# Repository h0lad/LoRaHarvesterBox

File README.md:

## What is this thing?

This generic LoRa base board is built around the ST STM32WLE5CC (RAK3172) and the TI BQ25570 energy harvester.

It is suitable for a wide range of applications, including:

- Meshtastic (router, sensor) or Meshcore
- LoRaWAN sensors
- Generic raw LoRa devices
- Or virtually any other custom project (ham balloon? Transmitter for tracking penguins?) that utilizes the modulation schemes (FSK, GFSK, MSK, GMSK) of the SX1262

For persistent data storage, an optional FRAM IC (Infineon FM24V10) can be added using I²C. A variety of sensors can additonaly integrated through I²C, SPI (on the back), or USART interfaces.

The power supply design is highly flexible: alongside standard JST-PH connectors, the board also supports very small LiPo batteries (commonly used in in-ear headphones or Bluetooth headsets), which can be soldered directly. Such batteries are readily available on AliExpress (e.g. 501010). The TI BQ25570 also supports exotic storages like Supercaps, LTO, etc.

## Features

### Energy

- Capable of handling a huge variety of energy storages: LiPo, LiFePo4, LTO, SIB, Supercap
- Starts boosting at 600mV. Maximum input voltage is 5.5V. 
- Up to 110mA can be used from the application
- MPPT
- Optional load-switch to switch on/off the entire STM32/LoRa-modem based on the VBAT_OK signal

### Microcontroller

Uses the standardized RAK housing which can house a variety of platforms (ESP32, STM32, etc.) with compatible pins. This variant uses the RAK3172  (ST STM32WLE5CC: 256Kb Flash, 64Kb RAM, 48MHz).

Exposed interfaces:

- 2x USART
- 1x I2C
- 1x SPI (back)
- 2x ADC connected to energy source (like solar) and and energy storage (like LiPos) using voltage dividers
- Multiple break-out pins for GPIOs on the back

### LoRa

Uses the Semtech SX1262 integrated within the STM32 housing. Multiple RAK variants available for 433/470/868/915MHz.

### Data Storage

Infineon FM24V10: 1-MBit non-volatile F-RAM for storing firmware updates, messages or mesurement data

## Physical Dimensions

This weirdo PCB format is designed around the cheapest water protected box from Aliexpress.

[Aliexpress, F-type, 63x58x35](https://de.aliexpress.com/item/1005005480970197.html)

## Design Decisions

### Why did you use the TI BQ25570?

It's the only energy harvester that supports up to 110mA peak current.

I'm not overly happy with this IC as it lacks a few useful features:

 - No I²C interface and ADC for reading voltages/currents

 - No Thermistor for switching off charging above and below specific temperatures

 - Doesn't switch off VOUT if the battery hits the lower threshold. It only signals it using a pin.

 - Rather annoying pin configuration. Layouting it doesn't make much fun.

 - It doesn't have interal high-precision resistors for configuring the voltage limits (VBAT_OV, etc.). Even with 1% tolerance resistors the resulting voltage ranges are barely acceptable due to error propagation.

 - Lowest possible battery voltage is 1.9V. This means we cannot utilize the full capacity of "exotic" storage types like LTO- and NaIon-cells.

Honestly - It's an old thing compared to the latest generation from ST or e-peas.
  
### Why not buying a "naked" ST STM32WLE5? 

Using a SoC module from RAK brings all the HF and impedancy matching. 

Everything else leaving the housing is not really critical signal wise.

Also it's not too expensive with 6€.

## Hardware

### Pin Configuration

#### ADC

| Signal | Pin | ADC Channel | Info | 
|:--------:|:----:|:-------------:|:------:|
| Energy Storage Voltage | PB3 | A0 | Voltage goes through a Voltage Divider |
| Energy Source Voltage  | PB4 | A1 | Voltage goes through a Voltage Divider |

#### USART

| Peripheral | TX Pin | RX Pin |
|:------------|:--------|:--------|
| UART1 | PB6 | PB7 |
| UART2 | PA2 | PA3 |

#### SWD

| Signal | Pin |
|:--------|:----|
| SWDIO | PA13 |
| SWCLK | PA14 |

##### SPI

| Signal | Pin |
|:--------|:----|
| SPI1, MOSI | PA7 |
| SPI1, MISO | PA6 |
| SPI1, CLK  | PA5 |
| SPI1, NSS  | PA4 |

#### LED

| Signal | Pin |
|:--------|:----|
| LED | PA8 |

#### MISC

| Signal | Pin |
|:--------|:----|
| VBAT_OK from TI BQ25570| PA15 |

### Resistors Values

**Warning:** 

You have to be super careful here. Don't trust your 1%-SMD-Resistor book from Aliexpress or Amazon. Measure each resistor with a high-resolution multimeter and then calculate the voltages according to the readings! A shabby Libreoffice Calc sheet can be found within the `docs` folder to do this.

I wrote a script for calculating resistor values here: [ti-bq25570-calculator](https://github.com/h0lad/ti-bq25570-calculator).

## Hardware Verification

### PCB Version v0.0.5

**Power Chain**

✅ 3.3V from TI BQ25570

✅ Charges power storage as defined with R_OV1 and R_OV2

✅ VBAT_OK signal with 3.3V LiPo attached as a storage

✅ Boosts 0.6V to 3.3V without energy storage attached

✅ Lower and upper  VBAT_OK threshold

✅ Power switch (TI TPS22917DBV)

**ST STM32WL55**

✅ Connect to the SWD interface using a ST-Link

**Findings**

1. The BQ25570 doesn't like my extremely noisy power supply as a storage emulation. It doesn't come up.

2. You have to be very careful as even the tolerance of 1% resistors (R_OV1 and R_OV2) might cause overcharging. So stay away from the hard limits of your battery.

## License

CERN Open Hardware Licence Version 2 - Strongly Reciprocal

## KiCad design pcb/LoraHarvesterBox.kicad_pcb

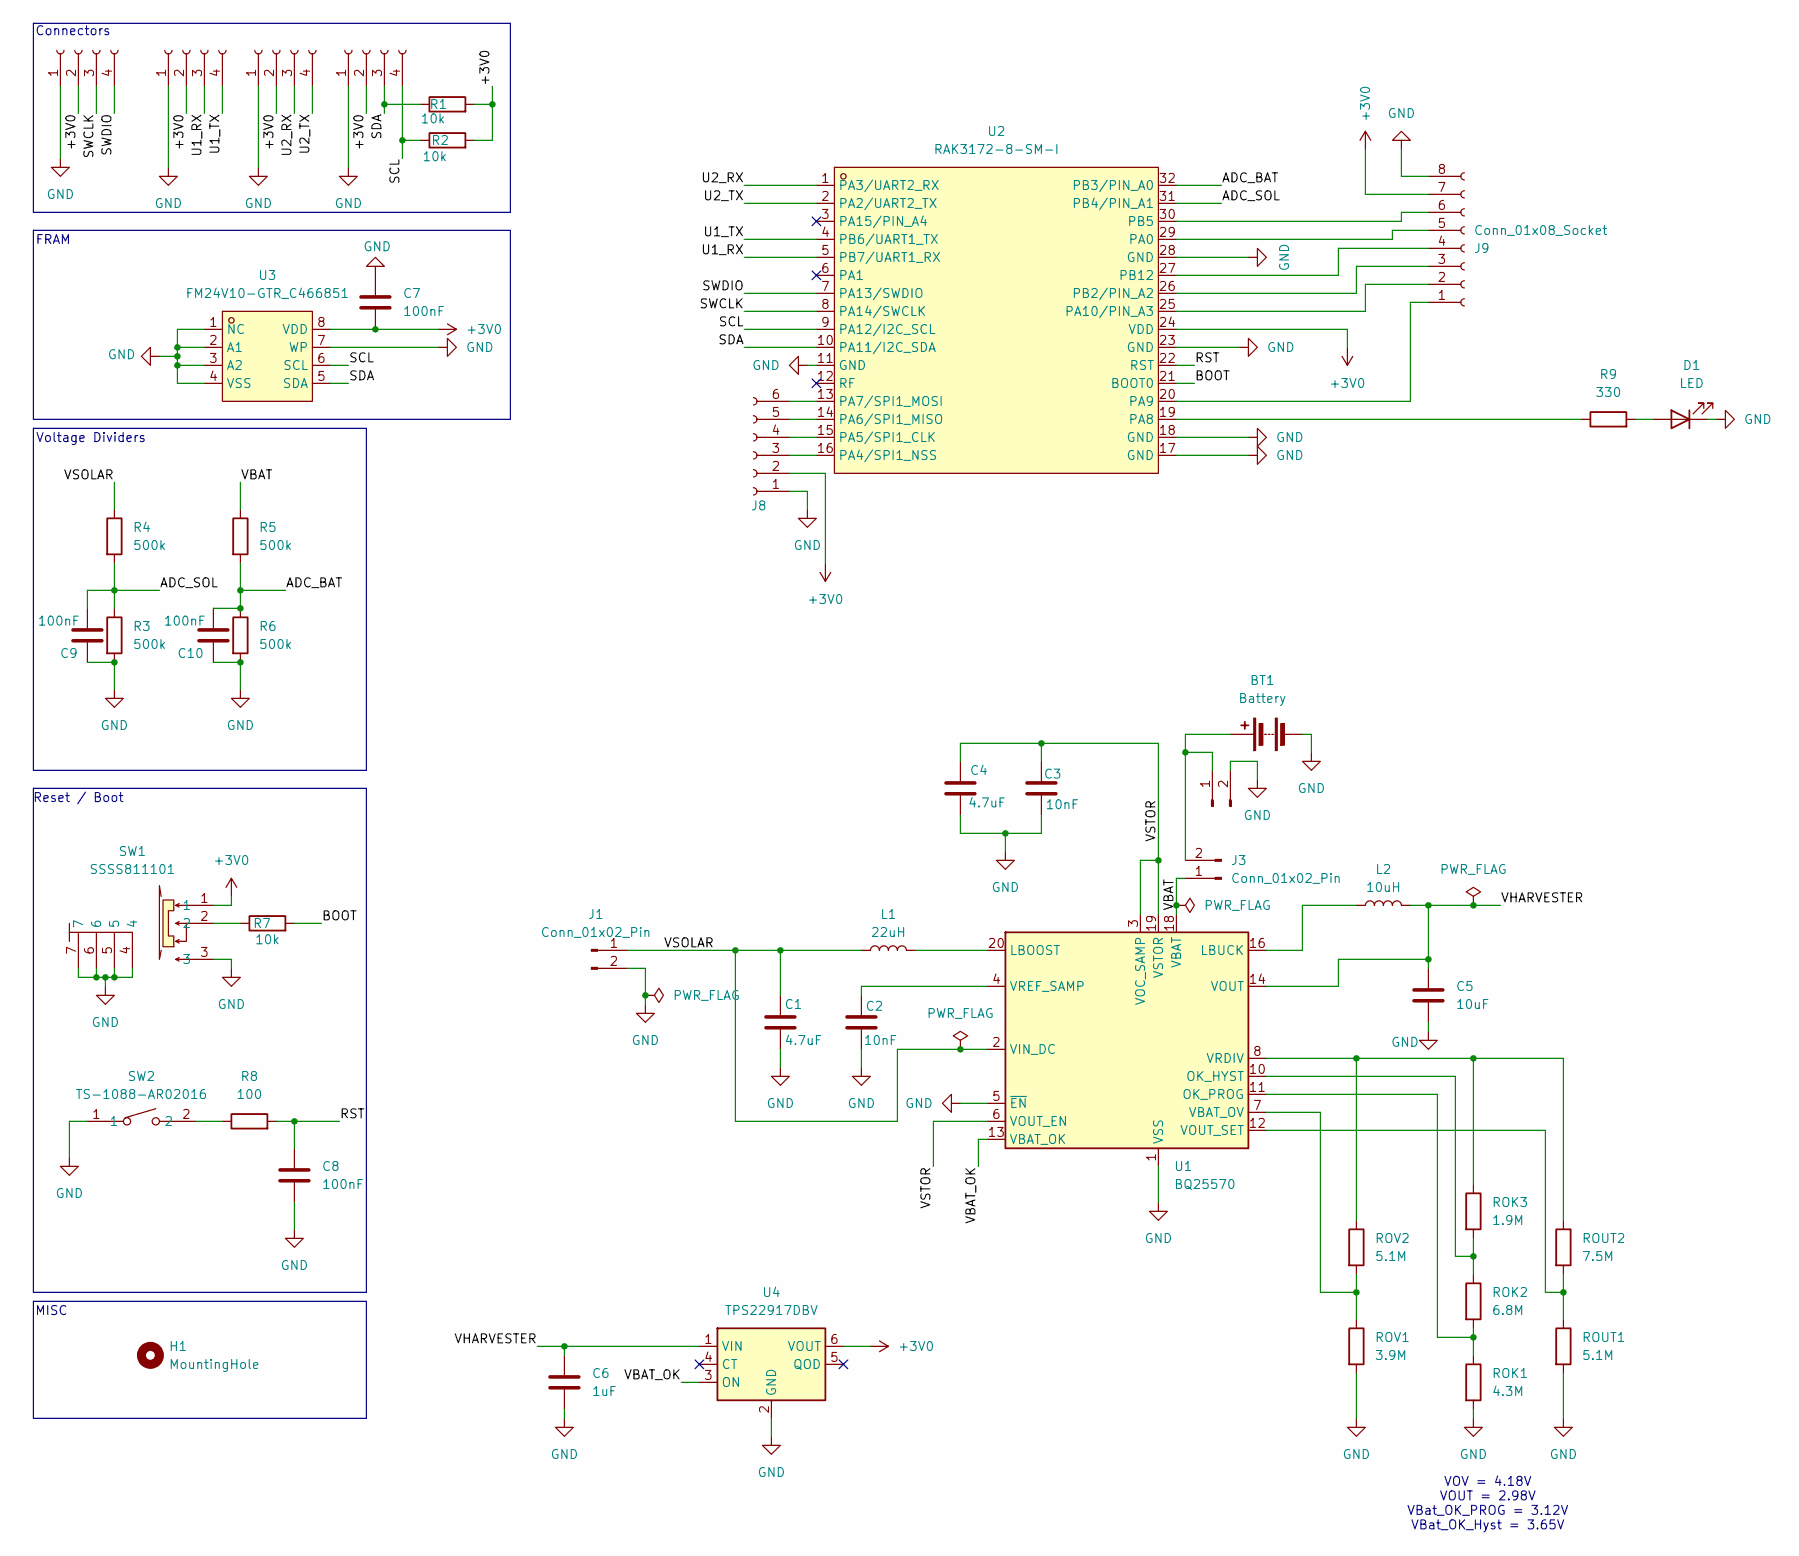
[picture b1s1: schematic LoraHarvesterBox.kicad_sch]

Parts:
BT1: Battery; 501010
C1: 4.7uF; C_0805_2012Metric_Pad1.18x1.45mm_HandSolder
C2, C3: 10nF; C_0603_1608Metric_Pad1.08x0.95mm_HandSolder
C4: 4.7uF; C_0603_1608Metric_Pad1.08x0.95mm_HandSolder
C5: 10uF; C_0805_2012Metric_Pad1.18x1.45mm_HandSolder
C6: 1uF; C_0603_1608Metric_Pad1.08x0.95mm_HandSolder
C7, C8, C9, C10: 100nF; C_0603_1608Metric_Pad1.08x0.95mm_HandSolder
D1: LED; LED_0603_1608Metric_Pad1.05x0.95mm_HandSolder
H1: MountingHole; MountingHole_2.2mm_M2
J1, J2: Conn_01x02_Pin; JST_PH_B2B-PH-K_1x02_P2.00mm_Vertical
J3: Conn_01x02_Pin; PinHeader_1x02_P2.54mm_Vertical
J4, J5, J6: Conn_01x04_Socket; JST_PH_B4B-PH-K_1x04_P2.00mm_Vertical
J7: Conn_01x04_Socket; JST_ZH_B4B-ZR_1x04_P1.50mm_Vertical
J8: Conn_01x06_Socket; PinHeader_1x06_P1.00mm_Vertical_SMD_Pin1Left
J9: Conn_01x08_Socket; PinHeader_1x08_P1.00mm_Vertical_SMD_Pin1Left
L1: 22uH; L1210
L2: 10uH; L1210
R1, R2: 10k; R_0603_1608Metric
R3, R4, R5, R6: 500k; R_0603_1608Metric_Pad0.98x0.95mm_HandSolder
R7: 10k; R_0603_1608Metric_Pad0.98x0.95mm_HandSolder
R8: 100; R_0603_1608Metric_Pad0.98x0.95mm_HandSolder
R9: 330; R_0603_1608Metric_Pad0.98x0.95mm_HandSolder
ROK1: 4.3M; R_0603_1608Metric_Pad0.98x0.95mm_HandSolder
ROK2: 6.8M; R_0603_1608Metric_Pad0.98x0.95mm_HandSolder
ROK3: 1.9M; R_0603_1608Metric_Pad0.98x0.95mm_HandSolder
ROUT1: 5.1M; R_0603_1608Metric_Pad0.98x0.95mm_HandSolder
ROUT2: 7.5M; R_0603_1608Metric_Pad0.98x0.95mm_HandSolder
ROV1: 3.9M; R_0603_1608Metric_Pad0.98x0.95mm_HandSolder
ROV2: 5.1M; R_0603_1608Metric_Pad0.98x0.95mm_HandSolder
SW1: SSSS811101; SW-SMD_SSSS811101; LCSC Part C109335
SW2: TS-1088-AR02016; SW-SMD_L3.9-W3.0-P4.45; LCSC Part C720477
U1: BQ25570; QFN-20-1EP_3.5x3.5mm_P0.5mm_EP2x2mm
U2: RAK3172-8-SM-I; WIRELM-SMD_32P-L15.5-W15.0-P1.00; LCSC Part C19723904
U3: FM24V10-GTR_C466851; SOIC-8_L5.0-W4.0-P1.27-LS6.0-BL; LCSC Part C466851
U4: TPS22917DBV; SOT-23-6

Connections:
+3V0: C7.2, J4.2, J5.2, J6.2, J7.2, J8.2, J9.7, R1.2, R2.2, SW1.1, U2.24 (VDD), U3.8 (VDD), U4.6 (VOUT)
/ADC_BAT: C10.2, R5.2, R6.1, U2.32 (PB3/PIN_A0)
/ADC_SOL: C9.2, R3.1, R4.2, U2.31 (PB4/PIN_A1)
/BOOT: R7.2, U2.21 (BOOT0)
/RST: C8.1, R8.2, U2.22 (RST)
/SCL: J7.4, R2.1, U2.9 (PA12/I2C_SCL), U3.6 (SCL)
/SDA: J7.3, R1.1, U2.10 (PA11/I2C_SDA), U3.5 (SDA)
/SWCLK: J4.3, U2.8 (PA14/SWCLK)
/SWDIO: J4.4, U2.7 (PA13/SWDIO)
/U1_RX: J5.3, U2.5 (PB7/UART1_RX)
/U1_TX: J5.4, U2.4 (PB6/UART1_TX)
/U2_RX: J6.3, U2.1 (PA3/UART2_RX)
/U2_TX: J6.4, U2.2 (PA2/UART2_TX)
/VBAT: J3.1, R5.1, U1.18 (VBAT)
/VBAT_OK: U1.13 (VBAT_OK), U4.3 (ON)
/VHARVESTER: C5.2, C6.2, L2.2, U1.14 (VOUT), U4.1 (VIN)
/VSOLAR: C1.1, J1.1, L1.1, R4.1, U1.2 (VIN_DC)
/VSTOR: C3.1, C4.1, U1.3 (VOC_SAMP), U1.6 (VOUT_EN), U1.19 (VSTOR)
GND: BT1.2 (-), C1.2, C2.2, C3.2, C4.2, C5.1, C6.1, C7.1, C8.2, C9.1, C10.1, D1.1 (K), J1.2, J2.2, J4.1, J5.1, J6.1, J7.1, J8.1, J9.8, R3.2, R6.2, ROK1.2, ROUT1.2, ROV1.2, SW1.3, SW1.4, SW1.5, SW1.6, SW1.7, SW2.1, U1.1 (VSS), U1.5 (~EN), U1.9 (VSS), U1.15 (VSS), U1.17 (VSS), U1.21 (VSS), U2.11 (GND), U2.17 (GND), U2.18 (GND), U2.23 (GND), U2.28 (GND), U3.1 (NC), U3.2 (A1), U3.3 (A2), U3.4 (VSS), U3.7 (WP), U4.2 (GND)
unnamed: BT1.1 (+), J2.1, J3.2
unnamed: D1.2 (A), R9.2
unnamed: J8.3, U2.16 (PA4/SPI1_NSS)
unnamed: J8.4, U2.15 (PA5/SPI1_CLK)
unnamed: J8.5, U2.14 (PA6/SPI1_MISO)
unnamed: J8.6, U2.13 (PA7/SPI1_MOSI)
unnamed: J9.1, U2.20 (PA9)
unnamed: J9.2, U2.25 (PA10/PIN_A3)
unnamed: J9.3, U2.26 (PB2/PIN_A2)
unnamed: J9.4, U2.27 (PB12)
unnamed: J9.5, U2.29 (PA0)
unnamed: J9.6, U2.30 (PB5)
unnamed: R7.1, SW1.2
unnamed: R8.1, SW2.2
unnamed: L1.2, U1.20 (LBOOST)
unnamed: L2.1, U1.16 (LBUCK)
unnamed: ROK2.1, ROK3.2, U1.10 (OK_HYST)
unnamed: ROK1.1, ROK2.2, U1.11 (OK_PROG)
unnamed: ROV1.1, ROV2.2, U1.7 (VBAT_OV)
unnamed: ROUT1.1, ROUT2.2, U1.12 (VOUT_SET)
unnamed: ROK3.1, ROUT2.1, ROV2.1, U1.8 (VRDIV)
unnamed: C2.1, U1.4 (VREF_SAMP)
unnamed: R9.1, U2.19 (PA8)

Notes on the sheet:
MISC
Connectors
Reset / Boot
VOV = 4.18V VOUT = 2.98V VBat_OK_PROG = 3.12V VBat_OK_Hyst = 3.65V
Voltage Dividers
FRAM

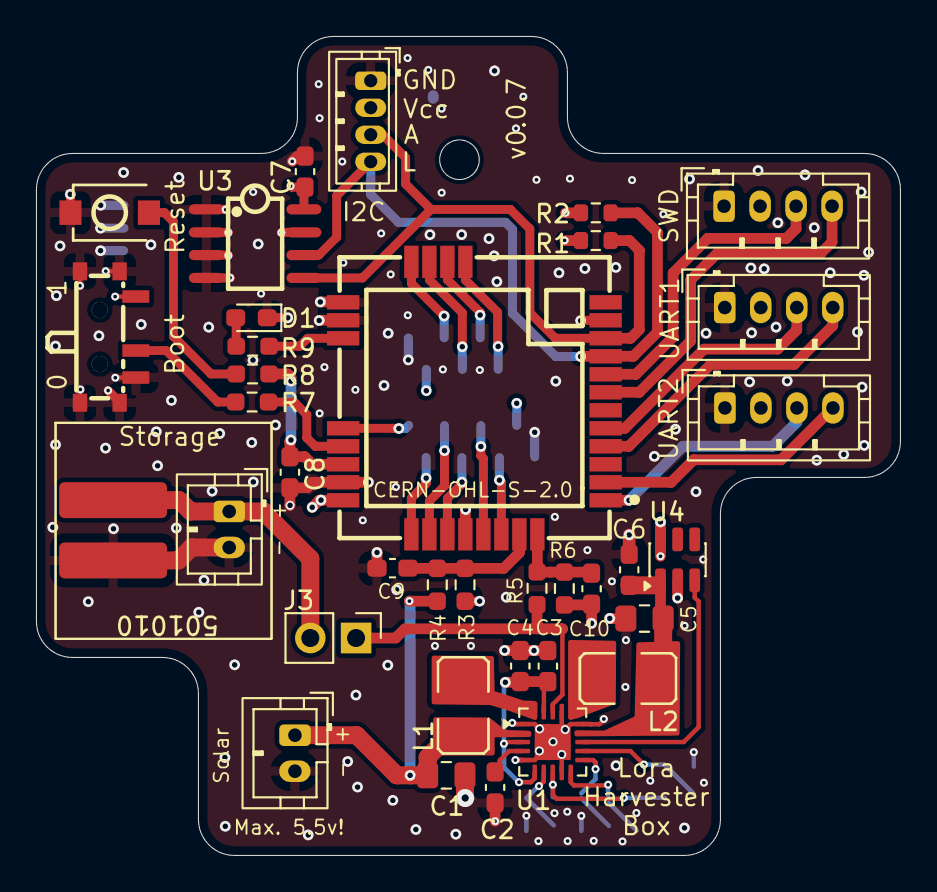
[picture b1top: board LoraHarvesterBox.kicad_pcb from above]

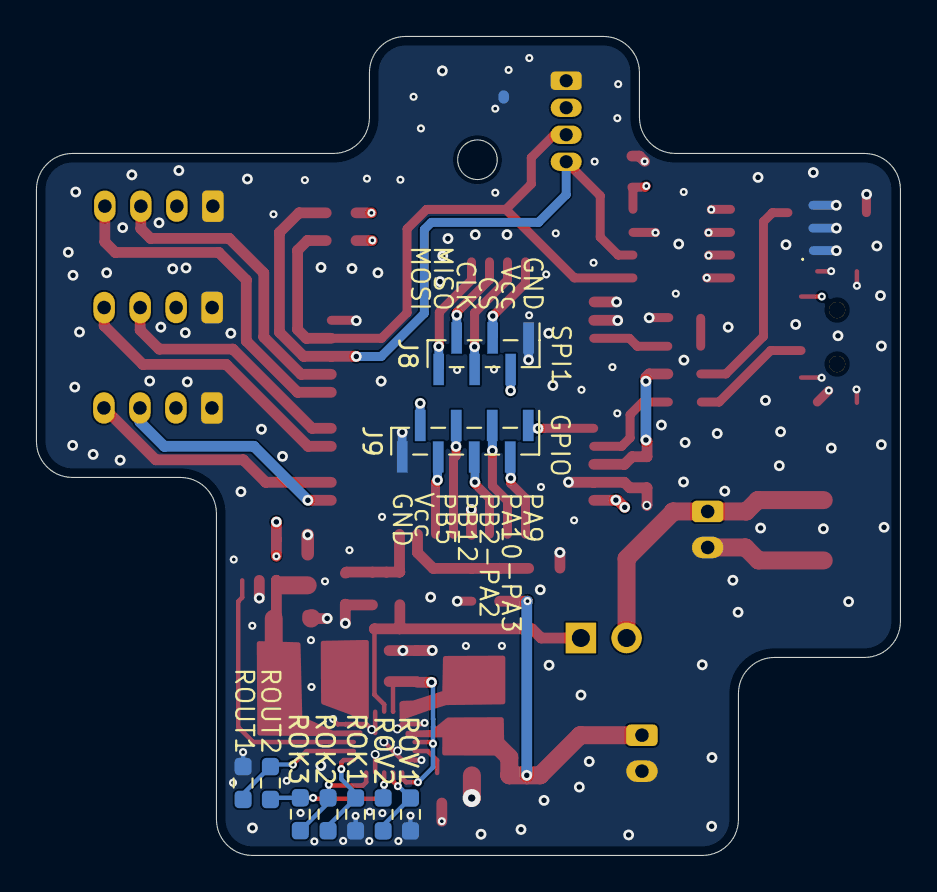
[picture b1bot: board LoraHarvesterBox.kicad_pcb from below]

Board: 4 copper layers, 48.0 x 45.5 mm, 46 parts (9 on the bottom side), 42 nets.

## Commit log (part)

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2025-11-23 README: add info regarding resistor tolerance impact on the voltages
2025-11-23 README: add missing words
2025-11-23 README: typo
2025-12-22 docs, pcb, sch: add missing buffer capacitor to power switch
2025-12-22 README: fix some leftovers and adjust formatting
2025-12-22 README: add information regarding lowest possible bat voltage
2026-01-11 README: add fitting box
2026-01-11 README: fix broken URL
2026-01-14 README: add picture of box
2026-01-16 pcb, sch: load switch now controls the entire 3.3V rail
    In the last version only the ST microcontroller was switched/on off by
    the load switch. This caused problems with the periphery: they stayed
    online with slowly fading into a brown out. This also fixes battery
    drain by half-dead sensors.
2026-01-16 pcb: clean up silk prints
2026-01-16 pcb: even more silk cleanups

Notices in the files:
pcb/LoraHarvesterBox.kicad_pcb:
CERN-OHL-S-2.0
